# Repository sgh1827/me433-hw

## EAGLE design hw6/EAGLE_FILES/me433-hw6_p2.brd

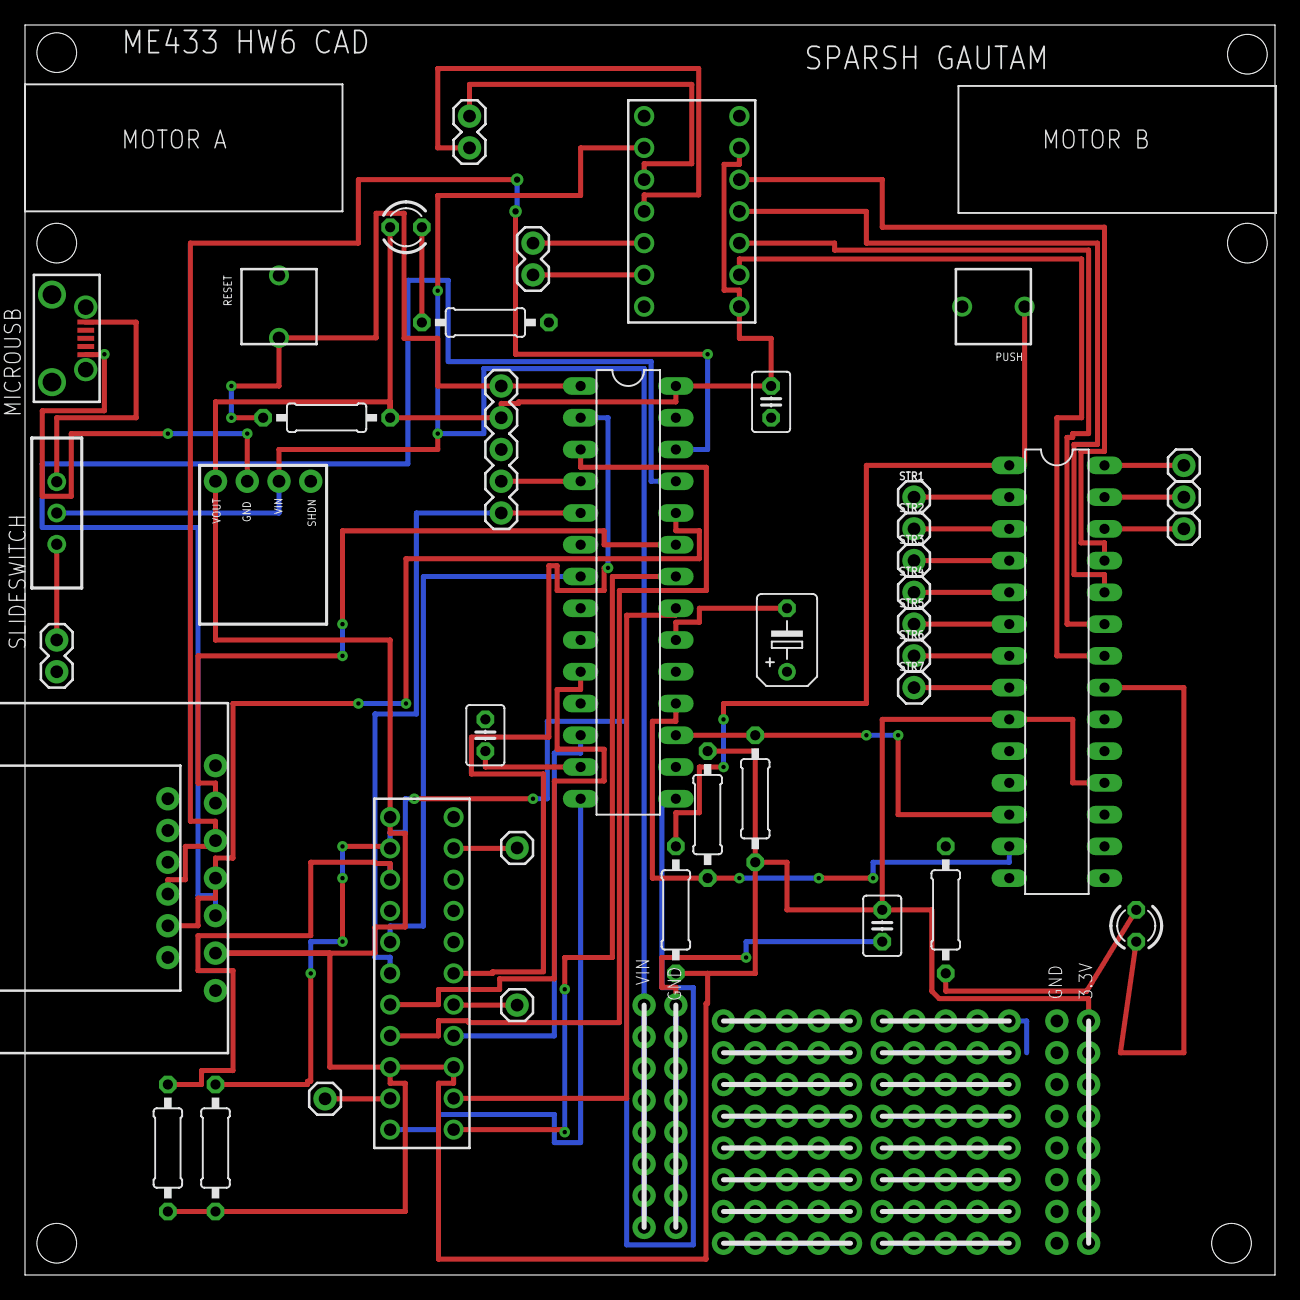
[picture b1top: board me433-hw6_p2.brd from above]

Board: 2 copper layers, 100.0 x 100.0 mm, 56 parts (0 on the bottom side), 67 nets.

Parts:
A: 1X02
B: 1X02
BAT: 1X02
C1, C3, C4: 0.1uF; C025-030X050
C2: 10uF; B45181B
HREF: 1X01
J1, J2, J3, J4, J5, J6, J7, J8, J9, J10, J11, J12, J13, J14: 1X08
LED1: RED; LED3MM
LED2: GREEN; LED3MM
PWDN: 1X01
R1, R5: 330; 0207/10
R2, R3, R4, R6: 10k; 0207/10
R7, R8: 4.7k; 0207/10
RESET: PUSH
STR, STR1, STR2, STR3, STR4, STR5, STR6, STR7, STR8, STR9, STR10: 1X01
U$1: PIC32MX170F256B; DIL28-3
U$2: MICROUSB
U$3: SLIDESWITCH
U$4: POLOLU3V3; POLULO3V3
U$5: SNAP; 1X05
U$6: H-BRIDGE
U$7: FRIEND
U$8: LCD
U$9: IO_EXPANDER; DIL28-3
U$10: CAMERA
USER: PUSH

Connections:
+3V3: C1.1, C4.1, J13.1, J13.2, J13.3, J13.4, J13.5, J13.6, J13.7, J13.8, LED1.A, R2.2, R3.2, R4.2, R6.2, R7.2, R8.2, U$1.28, U$4.1, U$5.2, U$6.P$8, U$6.P$13, U$8.2, U$9.9, U$9.18, U$10.P$1, U$10.P$9, U$10.P$14
+5V: U$2.1.VBUS, U$3.1
ADIR: U$6.P$9, U$9.22
APWM: U$6.P$10, U$9.23
B0-PGD-D4: U$1.4, U$5.4
B1-PGC-D5: U$1.5, U$5.5, U$10.P$6
B6: R7.1, U$1.15, U$10.P$2
B7: R8.1, U$10.P$3
B8: R3.1, U$1.17, U$9.12
B9: R4.1, U$1.18, U$9.13
B12: U$1.23, U$8.6
B13: U$1.24, U$7.2, U$8.4
B14: U$1.25, U$8.3
B15: U$1.26, U$7.3, U$8.5
BDIR: U$6.P$11, U$9.24
BPWM: U$6.P$12, U$9.25
D0: U$1.2, U$10.P$17
D1: U$1.3, U$10.P$8
D3: U$1.10, U$10.P$7
D7: U$1.7, U$10.P$5
GND: BAT.1, C1.2, C2.+, C3.2, C4.2, J12.1, J12.2, J12.3, J12.4, J12.5, J12.6, J12.7, J12.8, J14.1, J14.2, J14.3, J14.4, J14.5, J14.6, J14.7, J14.8, R1.1, R5.1, RESET.P$2, U$1.8, U$1.19, U$1.27, U$2.5.GND, U$4.2, U$5.3, U$6.P$1, U$7.6, U$8.1, U$9.10, U$9.15, U$9.16, U$9.17, U$10.P$22, USER.P$1
MCLR: R2.1, RESET.P$1, U$1.1, U$5.1
unnamed: LED1.K, R1.2
unnamed: C2.-, U$1.20
unnamed: C3.1, U$1.13
unnamed: LED2.A, U$9.21
unnamed: R6.1, U$9.1, USER.P$2
unnamed: LED2.K, R5.2
unnamed: B.2, U$6.P$3
unnamed: B.1, U$6.P$4
unnamed: A.2, U$6.P$5
unnamed: A.1, U$6.P$6
unnamed: STR.1, U$10.P$10
unnamed: PWDN.1, U$10.P$16
unnamed: HREF.1, U$10.P$21
unnamed: STR8.1, U$9.27
unnamed: STR9.1, U$9.28
unnamed: STR10.1, U$9.26
unnamed: STR1.1, U$9.2
unnamed: STR2.1, U$9.3
unnamed: STR3.1, U$9.4
unnamed: STR4.1, U$9.5
unnamed: STR5.1, U$9.6
unnamed: STR6.1, U$9.7
unnamed: STR7.1, U$9.8
unnamed: J1.8, J2.8, J3.8, J4.8, J5.8
unnamed: J1.7, J2.7, J3.7, J4.7, J5.7
unnamed: J1.6, J2.6, J3.6, J4.6, J5.6
unnamed: J1.5, J2.5, J3.5, J4.5, J5.5
unnamed: J1.4, J2.4, J3.4, J4.4, J5.4
unnamed: J1.3, J2.3, J3.3, J4.3, J5.3
unnamed: J1.2, J2.2, J3.2, J4.2, J5.2
unnamed: J1.1, J2.1, J3.1, J4.1, J5.1
unnamed: J6.8, J7.8, J8.8, J9.8, J10.8
unnamed: J6.7, J7.7, J8.7, J9.7, J10.7
unnamed: J6.6, J7.6, J8.6, J9.6, J10.6
unnamed: J6.5, J7.5, J8.5, J9.5, J10.5
unnamed: J6.4, J7.4, J8.4, J9.4, J10.4
unnamed: J6.3, J7.3, J8.3, J9.3, J10.3
unnamed: J6.2, J7.2, J8.2, J9.2, J10.2
unnamed: J6.1, J7.1, J8.1, J9.1, J10.1
RCK: U$1.12, U$10.P$15
RRST: U$1.21, U$10.P$13
V+: BAT.2, U$3.3
VIN: J11.1, J11.2, J11.3, J11.4, J11.5, J11.6, J11.7, J11.8, U$3.2, U$4.3, U$6.P$2
WR: U$1.14, U$10.P$11
WRST: U$1.22, U$10.P$12

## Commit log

2021-04-04 Create test
2021-04-04 Create deletme
2021-04-04 Create deleteme
2021-05-27 Create makefile
